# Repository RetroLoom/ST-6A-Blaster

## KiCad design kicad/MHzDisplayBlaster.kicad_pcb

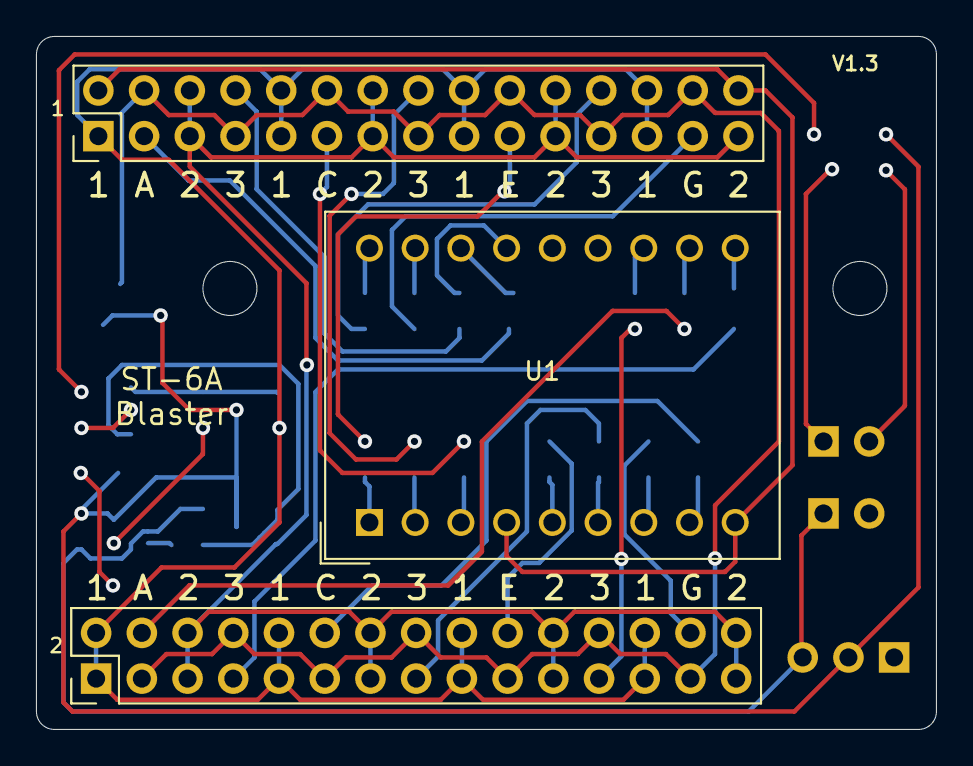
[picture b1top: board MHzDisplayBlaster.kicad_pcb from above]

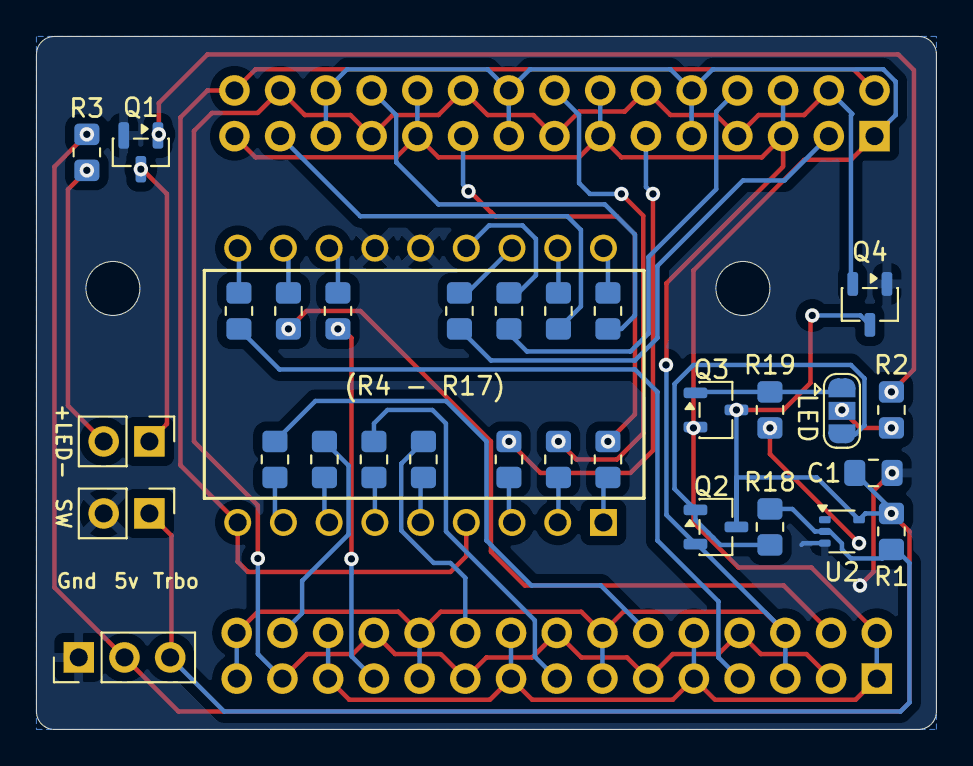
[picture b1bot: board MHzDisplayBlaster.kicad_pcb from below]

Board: 2 copper layers, 50.0 x 38.5 mm, 32 parts (29 on the bottom side), 42 nets.

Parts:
C1: 0.1uF; C_0805_2012Metric_Pad1.18x1.45mm_HandSolder
J1: Conn_02x15 DigitLHS; PinHeader_2x15_P2.54mm_Vertical
J2: Conn_02x15 DigitRHS; PinHeader_2x15_P2.54mm_Vertical
J3: INPUT; PinHeader_1x03_P2.54mm_Vertical
J4: LED; PinHeader_1x02_P2.54mm_Vertical
J5: SW; PinHeader_1x02_P2.54mm_Vertical
JP1: Jumper_3_Open; SolderJumper-3_P1.3mm_Open_RoundedPad1.0x1.5mm
Q1: 2N7002; SOT-23
Q2, Q3, Q4: Si2301; SOT-23-3
R1: 10k; R_0805_2012Metric_Pad1.20x1.40mm_HandSolder
R2, R18, R19: 470; R_0805_2012Metric_Pad1.20x1.40mm_HandSolder
R3, R4, R5, R6, R7, R8, R9, R10, R11, R12, R13, R14, R15, R16, R17: 330; R_0805_2012Metric_Pad1.20x1.40mm_HandSolder
U1: DC56-11GWA; DA56-11CGKWA
U2: 74LVC1G04; SOT-353_SC-70-5

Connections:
1: J1.1, J1.9, J1.10, J1.17, J1.18, J1.25, J1.26, J2.1, J2.2, J2.9, J2.10, J2.17, J2.18, J2.25, J2.26, Q3.2 (S)
2: J1.5, J1.6, J1.13, J1.14, J1.21, J1.22, J1.29, J2.5, J2.6, J2.13, J2.14, J2.21, J2.22, J2.29, J2.30, Q2.2 (S)
3: J1.4, J1.7, J1.12, J1.15, J1.20, J1.23, J1.28, J2.3, J2.8, J2.11, J2.16, J2.19, J2.24, J2.27, Q4.2 (S)
+5V: C1.2, J3.2, Q2.3 (D), Q3.3 (D), Q4.3 (D), R1.1, R3.2, U2.5 (VCC)
DIG1_A: J1.3, R4.2
DIG1_B: J1.8, R5.2
DIG1_C: J1.11, R6.2
DIG1_D: J1.16, R7.2
DIG1_E: J1.19, R8.2
DIG1_F: J1.24, R9.2
DIG1_G: J1.27, R10.2
DIG2_A: J2.4, R11.1
DIG2_B: J2.7, R12.1
DIG2_C: J2.12, R13.1
DIG2_D: J2.15, R14.1
DIG2_E: J2.20, R15.1
DIG2_F: J2.23, R16.1
DIG2_G: J2.28, R17.1
DP: J1.2, J1.30, U1.4 (DP1), U1.9 (DP2)
GND: C1.1, J3.1, J5.2, Q1.2 (S), Q4.1 (G), U1.13 (DIG2_CC), U1.14 (DIG1_CC), U2.3 (GND)
LED_SW: JP1.2 (C), R2.1
unnamed: J4.1, Q1.3 (D)
unnamed: J4.2, R3.1
unnamed: JP1.1 (A), Q3.1 (G), R19.2
unnamed: JP1.3 (B), Q2.1 (G), R18.2
unnamed: Q1.1 (G), R2.2
unnamed: R19.1, U2.4
unnamed: R4.1, U1.16 (DIG1_A)
unnamed: R5.1, U1.15 (DIG1_B)
unnamed: R6.1, U1.3 (DIG1_C)
unnamed: R7.1, U1.2 (DIG1_D)
unnamed: R8.1, U1.1 (DIG1_E)
unnamed: R9.1, U1.18 (DIG1_F)
unnamed: R10.1, U1.17 (DIG1_G)
unnamed: R11.2, U1.11 (DIG2_A)
unnamed: R12.2, U1.10 (DIG2_B)
unnamed: R13.2, U1.8 (DIG2_C)
unnamed: R14.2, U1.6 (DIG2_D)
unnamed: R15.2, U1.5 (DIG2_E)
unnamed: R16.2, U1.12 (DIG2_F)
unnamed: R17.2, U1.7 (DIG2_G)
Turbo: J3.3, J5.1, R1.2, R18.1, U2.2

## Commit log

2024-12-04 Switch to 74HC04
2024-12-28 Added 2N7000 MOSFET for LED header. KiCad 8
2024-12-28 Adjust mounting holes by 0.5mm
2025-03-18 Move mounting holes slightly by 0.25mm
2025-05-02 Add version silkscreen
2025-10-14 v1.2 - surface mount and better power management
2025-11-02 Added Individual segment resistors
2025-11-08 v1.3 - Anode resistors, mosfet power delivery, single channel inverter
2025-12-09 v1.4 - Swap Si2301 pins for proper source and drain, fix 2N7002 gate
2025-12-09 Updated Changes / Mostly unknown - probably zone fills
